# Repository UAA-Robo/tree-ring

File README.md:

# Tree Ring Imaging Machine (TRIM)
> **⚠️ Notice:** This project is no longer actively maintained.
>
> For an actively supported alternative, please see [FORGE](https://github.com/AnthonyvW/FORGE) — a low-cost, open-source imaging system built with off-the-shelf hardware. FORGE is designed to replace TRIM with improved support, extensibility, and easier hardware sourcing.

Documentation can be viewed at [uaa-robo.github.io/tree-ring](https://uaa-robo.github.io/tree-ring/) and in the docs folder.

This code controls the Amscope camera (our model is the MU500 and MU1000).

The following files are taken from the SDK provided by AmScope [here](https://amscope.com/pages/software-downloads) when you select your camera and model:
* amcam.py - this file provides an API for the camera. For more information about the API, see [API.pdf](API.pdf).
* simplest.py - this file provides a simple example that opens the camera and grabs frames from the camera, though it does not display these frames.
* qt.py - this file provides an example that grabs frames from the camera and renders them in a GUI.
* libamacam.dylib - needed for mac
* win/ - contains drivers and dlls needed for windows

We created the following files:
* camera.py - Interfaces with images from the amcam or the webcam if no amcam is present.
* gui.py - Displays a gui that the user can use to run the automation script. Displays camera feed.
* automationScript.py -  Script that rotates the motor to shift the platform and trigger the camera to take pctures.

## Setup & Running
For setup, run `python -m pip install -r requirements.txt` to install the python requirements needed.

To execute this program run `python gui.py` in this directory.

## Bundle program into an executable for Windows
To compile this program, double-click on the `build.bat` script. An executable will be generated
in the dist folder.

Note: When building the program in "windowed" mode or "noconsole", Windows thinks its a virus. Building
it with the console window attached when running prevents that from happening.

<!-- Old instructions -->
<!-- To compile this program go open the terminal in the directory of gui.py and run `python -m PyInstaller gui.py --onefile --windowed`. This will not work on Mac due to strict camera permission.

When building the program into a binary, Windows will throw a 'severe' threat warning. This is
because the software lacks an official Microsoft signature. To bypass this, open Windows Security,
click on 'Virus & threat protection,' and click on the link 'Manage settings' under 'Virus & threat
protection settings.' At the bottom of this menu there is a link to 'Add or remove exclusions.'
Add an exclusion of the type 'Folder,' and select the directory containing the program. Now running
the above command will successfully build the executable. -->

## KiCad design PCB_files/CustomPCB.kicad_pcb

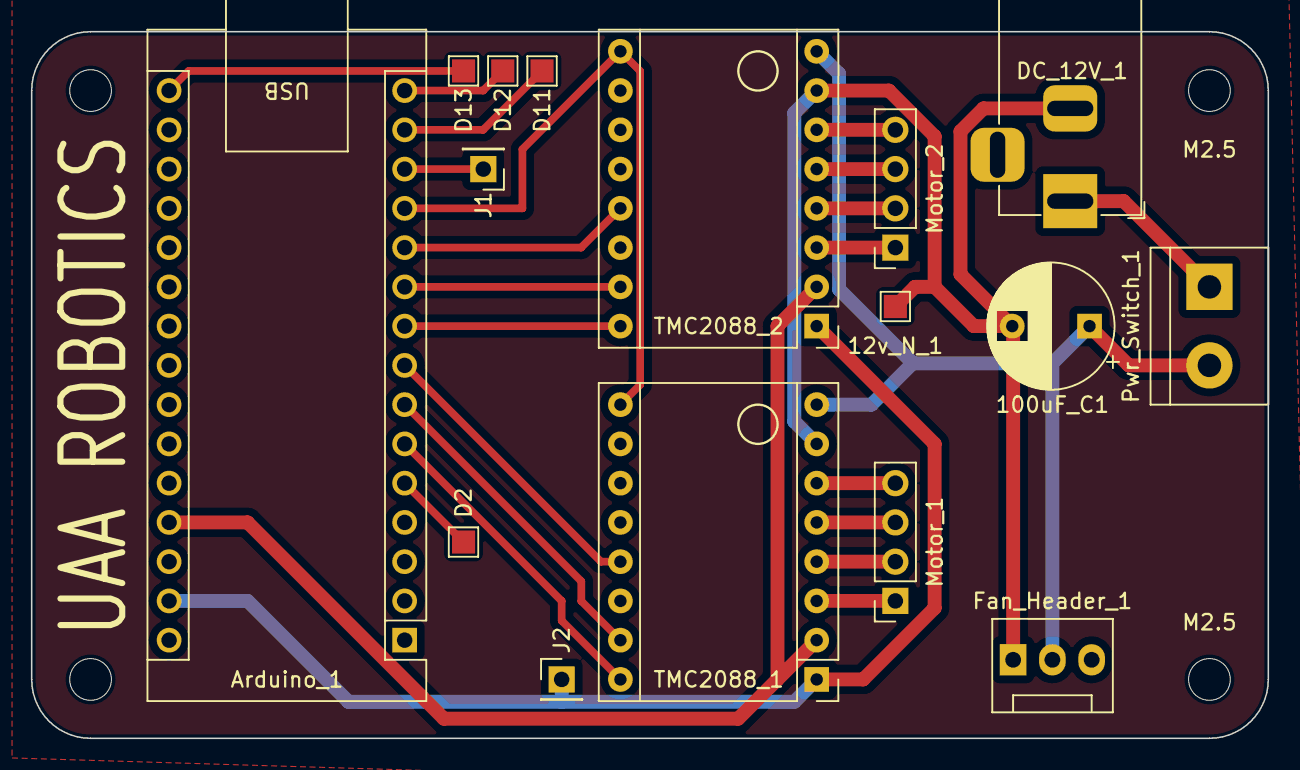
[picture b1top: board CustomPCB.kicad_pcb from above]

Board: 2 copper layers, 80.0 x 45.7 mm, 20 parts (0 on the bottom side), 25 nets.

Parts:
12v_N_1: TestPoint; TestPoint_Pad_1.5x1.5mm
100uF_C1: C 100; CP_Radial_D8.0mm_P5.00mm
Arduino_1: Arduino_Nano_v3.x; Arduino_Nano
D2, D11, D12, D13: TestPoint; TestPoint_Pad_1.5x1.5mm
DC_12V_1: Barrel_Jack_MountingPin; BarrelJack_Horizontal
Fan_Header_1: Fan_3pin; FanPinHeader_1x03_P2.54mm_Vertical
J1: Limit 1x1 Pin; PinHeader_1x01_P2.54mm_Vertical
J2: Conn_01x01_Socket; PinHeader_1x01_P2.54mm_Vertical
M2.5, M2.5#2, M2.5#3, M2.5#4: MountingHole_2.7mm_M2.5
Motor_1, Motor_2: Conn_01x04_Socket; PinSocket_1x04_P2.54mm_Vertical
Pwr_Switch_1: Screw_Terminal_01x02; TerminalBlock_bornier-2_P5.08mm
TMC2088_1, TMC2088_2: Pololu_Breakout_A4988; Pololu_Breakout-16_15.2x20.3mm

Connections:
/12v Negative: 12v_N_1.1, 100uF_C1.2, DC_12V_1.2, Fan_Header_1.1 (-), TMC2088_1.7 (GND), TMC2088_2.7 (GND)
/12v Positive: 100uF_C1.1, Fan_Header_1.2 (+), Pwr_Switch_1.2, TMC2088_1.8 (VMOT), TMC2088_2.8 (VMOT)
/12v Positive Terminal: DC_12V_1.1, Pwr_Switch_1.1
/D2 Breakout: Arduino_1.5 (D2), D2.1
/D11 Breakout: Arduino_1.14 (D11), D11.1
/D12 Breakout: Arduino_1.15 (D12), D12.1
/D13 Breakout: Arduino_1.16 (D13), D13.1
/Direction1: Arduino_1.9 (D6), TMC2088_2.16 (DIR)
/Direction2: Arduino_1.6 (D3), TMC2088_1.16 (DIR)
/Enable Pin: Arduino_1.12 (D9), TMC2088_1.9 (~ENABLE), TMC2088_2.9 (~ENABLE)
/Limit Pin: Arduino_1.13 (D10), J1.1
/Logic Negative: Arduino_1.29 (GND), J2.1, TMC2088_1.1 (GND), TMC2088_2.1 (GND)
/Logic Positive: Arduino_1.27 (+5V), TMC2088_1.2 (VDD), TMC2088_2.2 (VDD)
/Motor1A: Motor_2.1, TMC2088_2.3 (1B)
/Motor1B: Motor_2.2, TMC2088_2.4 (1A)
/Motor1C: Motor_2.3, TMC2088_2.5 (2A)
/Motor1D: Motor_2.4, TMC2088_2.6 (2B)
/Motor2A: Motor_1.1, TMC2088_1.3 (1B)
/Motor2B: Motor_1.2, TMC2088_1.4 (1A)
/Motor2C: Motor_1.3, TMC2088_1.5 (2A)
/Motor2D: Motor_1.4, TMC2088_1.6 (2B)
/Reset1: Arduino_1.11 (D8), TMC2088_2.13 (~RESET)
/Reset2: Arduino_1.8 (D5), TMC2088_1.13 (~RESET)
/Step1: Arduino_1.10 (D7), TMC2088_2.15 (STEP)
/Step2: Arduino_1.7 (D4), TMC2088_1.15 (STEP)

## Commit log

2023-12-20 Initial cv2 test - did not work :(
2023-12-20 test
2024-01-05 added arduino code
2024-01-05 added python script to change directions
2024-01-05 Added Limit Switch Control
2024-01-05 Initial Code from SDK
2024-01-05 Added Automatic Port Detection
2024-01-05 updated requirements.txt
2024-01-05 Added files todo
2024-01-07 Started camera implementation, testing with webcam for the time being
2024-01-07 Started microscope camera implementation, needs testing at lab
2024-01-10 Work on MU500
2024-01-10 Testing gui
2024-01-10 Added gitignore
2024-01-10 Converting to static methods
2024-01-10 removed captures
2024-01-10 File path hardcoding for now
2024-01-10 More webcam troubleshooting
2024-01-10 Testing camera
2024-01-10 It's working :)
2024-01-10 Some work on the MU500
2024-01-10 Webcam and MU500 work in GUI
2024-01-10 Added close method to Camera (unused)
2024-01-10 Oop forgot something
2024-01-10 Removed debug main call
2024-01-11 Added start automation button
2024-01-11 Added button callback
2024-01-11 Automation framework
2024-01-11 Added comments
2024-01-11 added Zeroing
2024-01-11 Added apptick
2024-01-12 Removed comments
2024-01-12 Image taking for microscope implemented, file path specification and individual image names todo
2024-01-12 Added docs
2024-01-12 Fixed future problem
2024-01-12 Camera streaming revised
2024-01-12 Protoype works!
2024-01-12 Updated todos
2024-01-12 Updated camera docstrings
2024-01-14 Wrapped Arduino code in class
2024-01-14 Created automation class as it's own thread
2024-01-14 Fixed mistake
2024-01-14 Threading now works with decorator
2024-01-14 Uncommented needed code
2024-01-16 Passing args to thread works
2024-01-16 Fixed threading and added logic for inputing core length
2024-01-16 Added shift logic and arduino check
2024-01-16 Added camera callback
2024-01-17 Added todos
2024-01-17 Added assignees
2024-01-22 Start button changes to stop button when the automation script is running
2024-01-22 Added open folder dialog, error boxes
2024-01-22 Removed requirement
2024-01-22 Changed tree length cm to mm
2024-01-23 Added another break call after sleep in start_automation()
2024-01-23 Added instructions for compiling into one app
2024-01-23 Formatted to dark mode
2024-01-23 Added camera window grow/shrink function
2024-01-23 Adjusted gui look
2024-01-23 Updated README.md with Windows build instructions
2024-01-23 Added movement length adjustment
2024-01-24 Updated Arduino readme
2024-01-24 Added TODOs to readme
2024-01-24 Added first CAD model
2024-01-24 Added doc link
2024-01-28 Fixed text color and button size
2024-01-28 Updated gui.py to meet styling standards
2024-01-28 Updated includes in gui
2024-01-28 Added function types to match style guide
2024-01-28 Updates to match style guidelines
2024-01-28 Added tree ring length logic
2024-01-28 Added timestamp it image name
2024-01-28 Added title
2024-01-28 Added automation status messages
2024-01-28 Started instructions in docsify
2024-01-28 Change image folder location to desktop on mac
2024-01-29 Added template for documentation
2024-01-29 Cleaned up repo a bit
2024-01-29 Improved error handling
2024-01-29 Update gui.py and uploaded most recent build
2024-01-29 Added fix to stop slowness (I think)
2024-01-29 Fixed some merge bugs
2024-01-29 Formatted gui a bit more for windows
2024-01-29 Bug fixes
2024-01-30 Updated comments
2024-01-30 Added Camera class documentation
2024-01-30 Uploaded executable
2024-01-30 Fixed image file naming bug
2024-01-30 Uploaded latest build
2024-01-31 Added readme updaates
2024-01-31 Brought code to standards
2024-01-31 Added camera image quality adjustment methods
2024-01-31 Took out zeroing functionality
2024-02-01 Added gui input for image name
2024-02-01 Added automation logic for custom image names
2024-02-01 Updated automation names with _
2024-02-01 Reduced automation wait time
2024-02-01 Took out some sleeps
2024-02-05 Added sliders, weird bug where temp and tint always reset to lowest value
2024-02-05 edits at ebl
2024-02-05 Working but buggy
2024-02-05 Slider widget now only created when needed
2024-02-06 Added PCB Files
2024-02-06 updated PCB for JLCPCB's tolerances
2024-02-07 Updated Arduino Documentation
2024-02-07 Added docs for automaation
2024-02-07 Added GUI and Automation docs and updated some variable names to make more sense
2024-02-07 Docs formatting
2024-02-07 Added electronics box stl
2024-02-10 Updated Driver for TMC2088 and Swapped pins 7 and 6
2024-02-10 removed unneeded backups
2024-02-12 Pause button added
2024-02-12 More troubleshooting
2024-02-13 Fixed temp/tint bug
2024-02-13 PCB V2
2024-02-14 Updated Readme Progress
2024-02-19 Added function prototypes and comments
2024-02-20 Morning fixes
2024-02-20 Started color testing
2024-02-20 Bug fixes post merge
2024-02-20 It's working!
2024-02-20 Actually not working
2024-03-07 Fixed Shift lengths
2024-03-09 Added venv to gitignore
2024-03-13 Adjusted Wait Time
2024-03-13 fixed last image wait time.
2024-03-18 Added 1-second sleep to allow for still image capture
2024-03-21 Messed with default camera options
2024-03-22 3.22.2024 Meeting
2024-03-22 changed aurdino
2024-03-22 made motor not power on
2024-03-22 added reset
2024-03-23 Keeps track of shift length now
2024-03-23 added dynamic wait time
2024-03-27 Changed position (check)
2024-03-28 Fixed Distance Moved Error
2024-04-03 Added venv to .gitignore
2024-04-03 Updated defaults for camera settings based on last meeting
2024-04-05 Allowed webcam image capture again
2024-04-05 Removed prints
2024-04-05 Moved pause button by start/stop
2024-04-12 Implemented single image capture
2024-04-24 Started putting new camera settings in sliders
2024-04-24 Update cam config
2024-04-24 Added Linear Checkbox
2024-04-24 Added PNG/JPG combobox
2024-04-29 Wrapped QSliders in a QWidget with increment/decrement buttons
2024-04-29 Added curve TM option to Sliders
2024-04-29 Changed image file format options
2024-04-29 Updated docs and defaults
2024-04-29 Removed unnecessary comments
2024-04-30 Changed default camera settings to optimal
2024-05-02 Added image path selection options
2024-05-02 Deleted dist
2024-05-02 Added image number selection option
2024-05-02 Added hover button visual changes to camera options
2024-05-03 Updated sharpness default to 500 and docs
2024-05-04 General updates
2024-05-12 Added auto-exposure enable option to Camera Options, and allowed camera image settings to be modified even if the microscope isn't used
2024-05-13 Changed slider defaults to match optimal settings in camera.py
2024-05-13 Delete run.bat
    Debug file unnecessary in main branch
2024-05-13 Added build script
2024-05-13 Fixed missing entry in docs sidebar
2024-05-26 Fixed hue not changing on slider
2024-06-05 Updated SDK
2024-06-05 Made still image resolution dependent on the camera instead of hardcoded
2024-06-05 Added instructions for upgrading the camera and updated build.bat
2024-11-19 Updated Title
2024-11-21 Updated Instructions
2024-11-21 Cleaned up docs
2024-11-21 Added 3D models for the enclosure
2024-11-21 Added missing links in docs
2024-11-22 updated requirements.txt to handle incompatible numpy version
2024-12-09 Added new CADs
